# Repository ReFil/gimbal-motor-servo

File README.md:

# gimbal-motor-servo
 An ESC and firmware suitable for sensored 2205 gimbal motors

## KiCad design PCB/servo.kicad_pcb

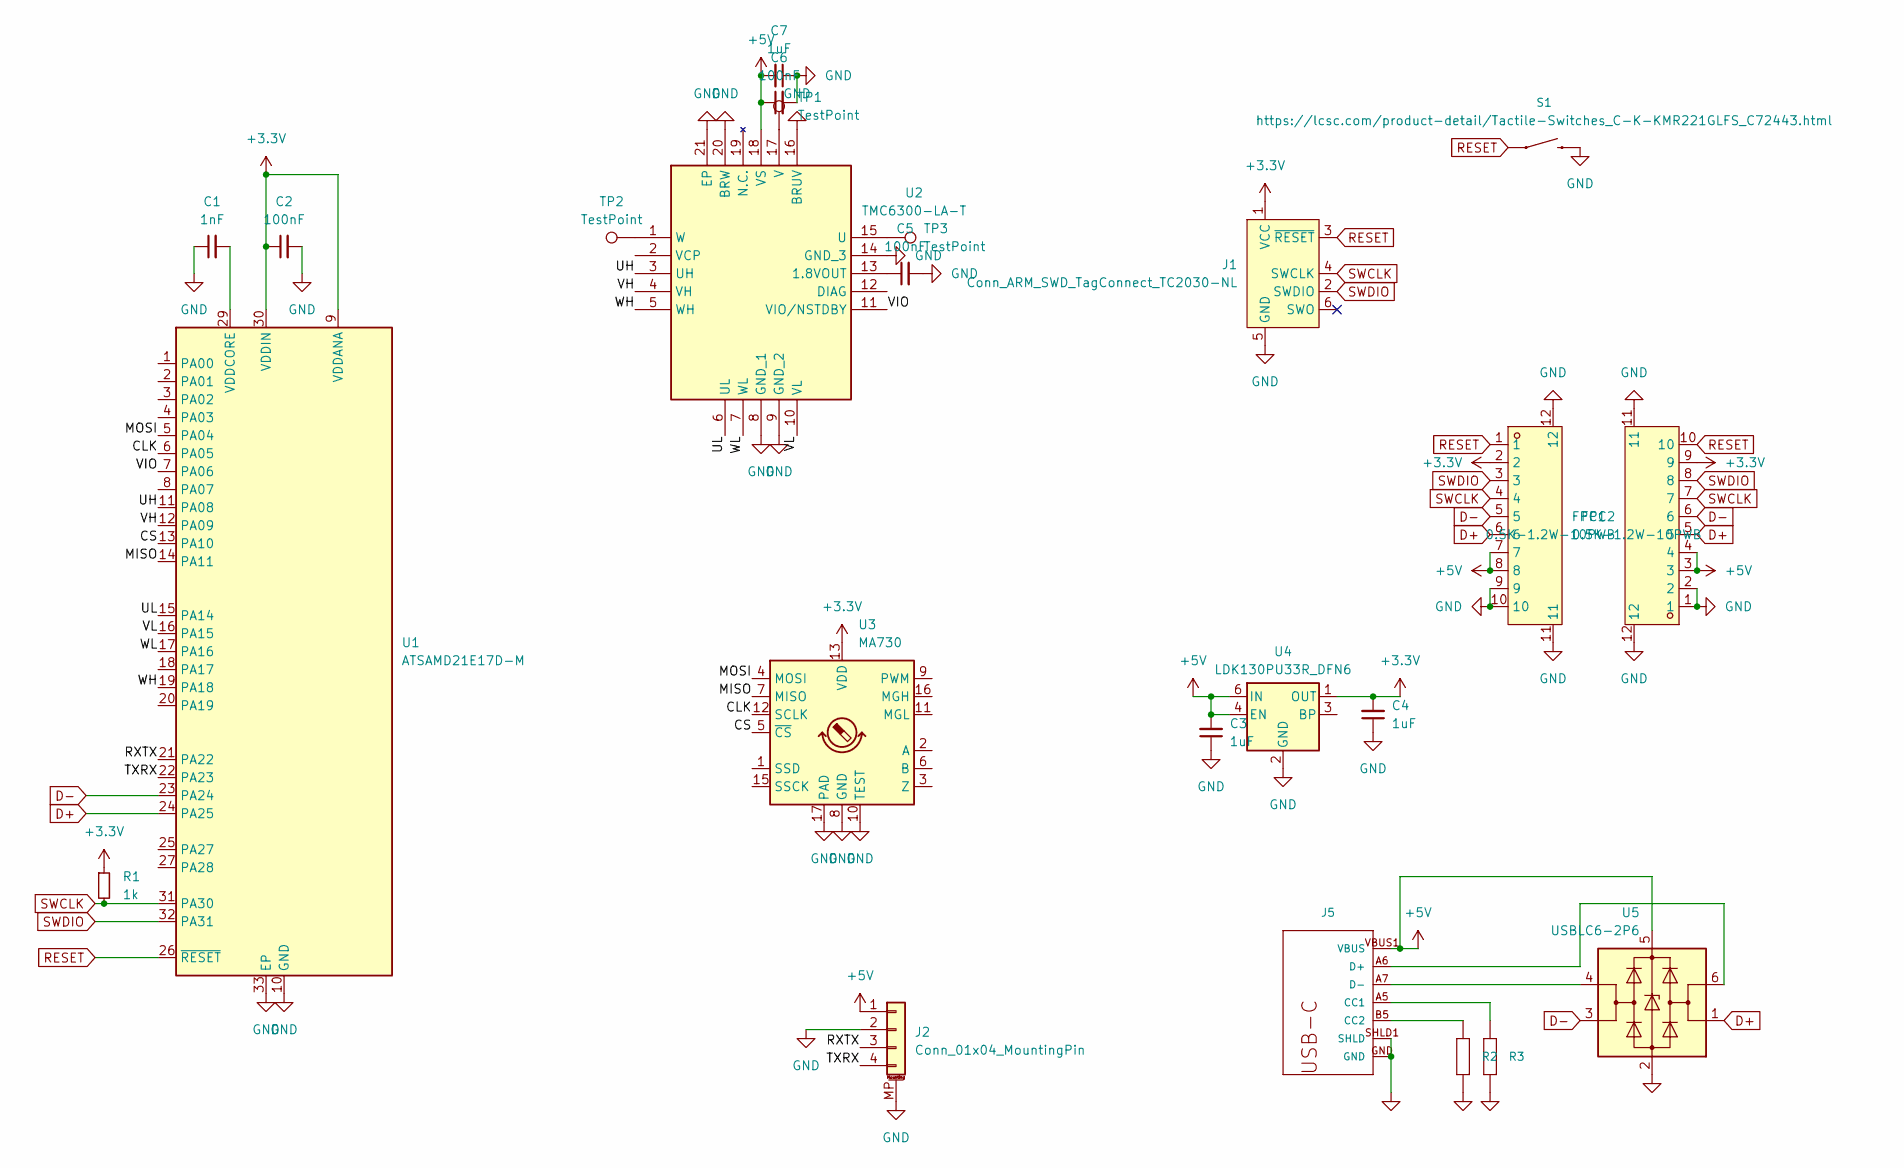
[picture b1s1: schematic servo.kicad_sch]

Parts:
C1: 1nF; C_0402_1005Metric; LCSC Part Number C129637
C2, C5, C6: 100nF; C_0402_1005Metric; LCSC Part Number C2169363
C3, C4, C7: 1uF; C_0402_1005Metric; LCSC Part Number C2169363
FPC1, FPC2: 0.5K-1.2W-10PWB; CONN-SMD_10P-P0.50_0.5K-1.2W-10PWB; LCSC Part C5337033
J1: Conn_ARM_SWD_TagConnect_TC2030-NL; Tag-Connect_TC2030-IDC-NL_2x03_P1.27mm_Vertical
J2: Conn_01x04_MountingPin; Molex_Pico-EZmate_78171-0004_1x04-1MP_P1.20mm_Vertical; LCSC Part C2840019
J5: XKB-USB-C16PIN; XKB-USB-C-16P; LCSC Part C319148
R1: 1k; R_0402_1005Metric; LCSC Part C2906899
R2, R3: 5.1k; R_0402_1005Metric; LCSC Part C25941
S1: MOMENTARY-SWITCH-SPST-SMD-4.6X2.8MM; TACTILE_SWITCH_SMD_4.6X2.8MM; LCSC Part C269272
TP1, TP2, TP3: TestPoint; TestPoint_Pad_D1.5mm
U1: ATSAMD21E17D-M; QFN-32-1EP_5x5mm_P0.5mm_EP3.6x3.6mm; LCSC Part C614245
U2: TMC6300-LA-T; QFN40P300X300X90-21N; Mouser Part Number 700-TMC6300-LA-T
U3: MA730; QFN-16-1EP_3x3mm_P0.5mm_EP1.45x1.45mm
U4: LDK130PU33R_DFN6; DFN-6_1.3x1.2mm_P0.4mm; LCSC Part C5267896
U5: USBLC6-2P6; SOT-666; LCSC Part C15999

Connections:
+3.3V: C2.1, C4.2, FPC1.2, FPC2.9, J1.1 (VCC), R1.1, U1.9 (VDDANA), U1.30 (VDDIN), U3.13 (VDD), U4.1 (OUT)
+5V: C3.2, C6.1, C7.2, FPC1.7, FPC1.8, FPC2.3, FPC2.4, J2.1, J5.VBUS1 (VBUS), J5.VBUS2 (VBUS), U2.18 (VS), U4.4 (EN), U4.6 (IN), U5.5 (VBUS)
/CLK: U1.6 (PA05), U3.12 (SCLK)
/CS: U1.13 (PA10), U3.5 (~CS)
/MISO: U1.14 (PA11), U3.7 (MISO)
/MOSI: U1.5 (PA04), U3.4 (MOSI)
/RXTX: J2.3, U1.21 (PA22)
/TXRX: J2.4, U1.22 (PA23)
/UH: U1.11 (PA08), U2.3 (UH)
/UL: U1.15 (PA14), U2.6 (UL)
/VH: U1.12 (PA09), U2.4 (VH)
/VIO: U1.7 (PA06), U2.11 (VIO/NSTDBY)
/VL: U1.16 (PA15), U2.10 (VL)
/WH: U1.19 (PA18), U2.5 (WH)
/WL: U1.17 (PA16), U2.7 (WL)
D+: FPC1.6, FPC2.5, U1.24 (PA25), U5.1 (I/O1)
D-: FPC1.5, FPC2.6, U1.23 (PA24), U5.3 (I/O2)
GND: C1.1, C2.2, C3.1, C4.1, C5.2, C6.2, C7.1, FPC1.9, FPC1.10, FPC1.11, FPC1.12, FPC2.1, FPC2.2, FPC2.11, FPC2.12, J1.5 (GND), J2.2, J2.MP (MountPin), J5.GND, J5.GND2 (GND), J5.SHLD1 (SHLD), R2.1, R3.1, S1.3 (2), S1.4 (2), U1.10 (GND), U1.28 (GND), U1.33 (EP), U2.8 (GND_1), U2.9 (GND_2), U2.14 (GND_3), U2.16 (BRUV), U2.20 (BRW), U2.21 (EP), U3.8 (GND), U3.10 (TEST), U3.17 (PAD), U4.2 (GND), U5.2 (GND)
unnamed: J5.A5 (CC1), R3.2
unnamed: J5.B5 (CC2), R2.2
unnamed: J5.A6 (D+), J5.B6 (D+), U5.6 (I/O1)
unnamed: J5.A7 (D-), J5.B7 (D-), U5.4 (I/O2)
unnamed: C1.2, U1.29 (VDDCORE)
unnamed: C5.1, U2.13 (1.8VOUT)
unnamed: TP3.1, U2.15 (U)
unnamed: TP1.1, U2.17 (V)
unnamed: TP2.1, U2.1 (W)
RESET: FPC1.1, FPC2.10, J1.3 (~RESET), S1.1, S1.2 (1), U1.26 (~RESET)
SWCLK: FPC1.4, FPC2.7, J1.4 (SWCLK), R1.2, U1.31 (PA30)
SWDIO: FPC1.3, FPC2.8, J1.2 (SWDIO), U1.32 (PA31)

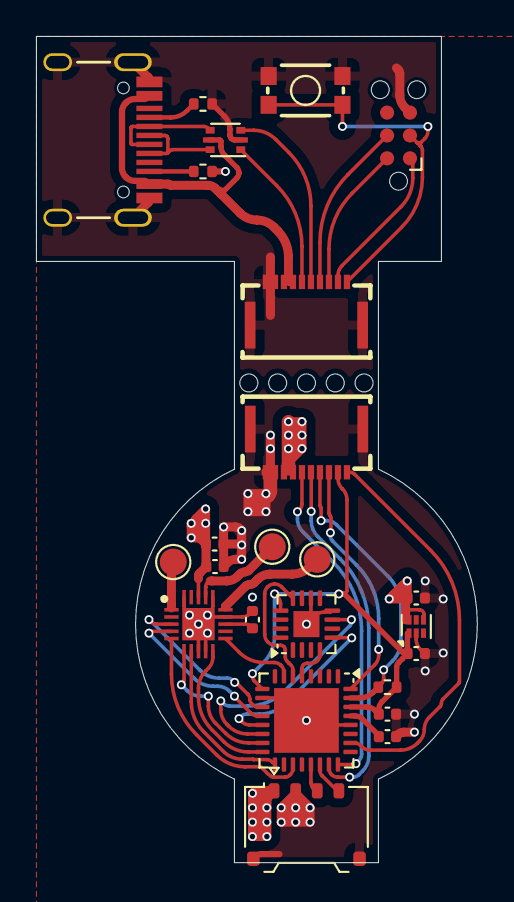
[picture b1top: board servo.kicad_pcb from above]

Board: 4 copper layers, 24.5 x 45.9 mm, 24 parts (0 on the bottom side), 30 nets.

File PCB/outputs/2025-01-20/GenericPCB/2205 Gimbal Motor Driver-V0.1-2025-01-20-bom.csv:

"Value","Designator","Footprint","LCSC Part Number","Digikey Part Number","Comments"
"1nF","C1","C_0402_1005Metric","C129637","",""
"100nF","C2,C5,C6","C_0402_1005Metric","C2169363","",""
"1uF","C3,C4,C7","C_0402_1005Metric","C2169363","",""
"0.5K-1.2W-10PWB","FPC1,FPC2","CONN-SMD_10P-P0.50_0.5K-1.2W-10PWB","C5337033","",""
"Conn_01x04_MountingPin","J2","Molex_Pico-EZmate_78171-0004_1x04-1MP_P1.20mm_Vertical","C2840019","",""
"XKB-USB-C16PIN","J5","XKB-USB-C-16P","C319148","","4 TH Pads"
"1k","R1","R_0402_1005Metric","C2906899","",""
"5.1k","R2,R3","R_0402_1005Metric","C25941","",""
"MOMENTARY-SWITCH-SPST-SMD-4.6X2.8MM","S1","TACTILE_SWITCH_SMD_4.6X2.8MM","C269272","",""
"ATSAMD21E17D-M","U1","QFN-32-1EP_5x5mm_P0.5mm_EP3.6x3.6mm","C614245","",""
"LDK130PU33R_DFN6","U4","DFN-6_1.3x1.2mm_P0.4mm","C5267896","",""
"MA730","U3","QFN-16-1EP_3x3mm_P0.5mm_EP1.45x1.45mm","","",""
"TMC6300-LA-T","U2","QFN40P300X300X90-21N","C5274455","",""
"USBLC6-2P6","U5","SOT-666","C15999","",""

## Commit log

2025-01-09 initial schematic
2025-01-09 Commit currrent work
2025-01-11 commit initial firmware
2025-01-11 Update pcb
2025-01-16 Commit current PCB progress
2025-01-20 Complete PCB
2025-01-20 Gerbers and changes
2025-02-16 Latest fw
2025-04-28 Minor revisions
